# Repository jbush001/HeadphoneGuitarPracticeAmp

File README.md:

## Background

I was looking for a headphone guitar amp with the following features:

- Integrated guitar plug: Doesn't require an extra cable or have a box
  flopping around.
- Rechargeable battery
- Flexible set of basic effects with decent quality: distortion, reverb,
  amp simulation, etc.
- Built-in metronome

Although there are a number of commercially available headphone amps that
each support some of  these, surprisingly, none supported all of them, so
I decided to build my own. The heart of this is an ARM microcontroller,
which processes the audio signal and applies digital effects. The hardware
consists of a custom printed circuit board in a 3D printed enclosure.

## Setup (MacOS)

### Initial bits

Set up the environment (only required once)

    ./setup.sh

### CAD

This uses the build123d package for all CAD design. When starting a new terminal/session:

    source ./venv/bin/activate

You can regenerate the generated STL file by typing:

    python enclosure.py

The STL file can be viewed with a system viewer.

(Note, this may not work from the VSCode terminal, as it needs to separately set
the python environment).

### Schematic

Install the latest version of KiCAD from here <https://www.kicad.org/download/>.

Launch the editor, then, from the main project window, launch the
"Plugin and Content Manager." Search for "Fabrication Toolkit," and
click install, followed by "apply pending changes."

The fabrication toolkit is important not only because it fixes component
orientation differences between KiCad's symbols (which follow the IPC standard),
and JLCPCB's <https://jlcpcb.com/> library, which is based on the orientation
in the tape reel. If components are still misaligned (which can be seen from
the preview on JLCPCB's website), add the field FT Rotation Offset to the
symbol properties (it will rotate the field counter clockwise).

The fabrication outputs can be generated by clicking
Tools->External Plugins->Fabrication Toolkit from the PCB viewer. Output files
will be in the directory logic_board/production. The ones that are needed by
JLCPCB are:
- logic_board.zip. Upload using the 'Add Gerber' button
- bom.csv. After turning on the PCB Assembly switch and clicking next, can
  choose this file under the 'upload BOM' button.
- positions.csv. This is uploaded under the 'upload CPL' button.

Some through hole parts need to be hand soldered and are not included in the
assembly positions or BOM.

When changing part values or adding new parts, be sure to populate the
LCSC Part Number (note: case sensitive) attribute on the Symbol Properties
pane *from the schematic editor* (these will be copied to the PCB when
"Update PCB From Schematic" is pressed)

### Software

Software can be uploaded using the ST-Link v2 programmer (these are available in lots
of places).

<https://www.adafruit.com/product/2548?srsltid=AfmBOoq6BzHUY0KrrB4XPQAl0OvnK3d9qYIsi6UlSETSzX4CNc_bk4Xj>

This uses a standard SOICBite connector for debugging (e.g.
<https://www.pomonaelectronics.com/products/test-clips/ic-test-clips/soic-clip-8-pin>),
with the following pinout:

| Board Pad | Function    | ST-Link Pin |
|-----------|-------------|-------------|
|     1     | VCC (3.3v)  |     n/c     |
|     2     | SWDIO       |      2      |
|     3     | SWCLK       |      6      |
|     4     | GND         |      3      |
|     5     | UART TX     |      -      |
|     6     | UART RX     |      -      |
|     7     | nRST        |      1      |
|     8     | GPIO        |      -      |

Note: for the cheapo aluminum STLink clones, you don't want to connect VCC.

For UART, a serial to USB converter like
<https://www.deshide.com/product-details_SH-U09C2.html> can be used. It must be
set for 3.3v output. Connect the TX pin on the converter to the RX pin on the
board and vice versa. You'll need a Dupont Y jumper to share the ground
between the two connectors.

This uses the STM32H7 microcontroller.

Install ARM toolchain (MacOS)

    brew tap ArmMbed/homebrew-formulae
    brew install arm-none-eabi-gcc stlink

(Linux):

    sudo apt-get install gcc-arm-none-eabi binutils-arm-none-eabi

### Notebooks

    jupyter notebook notebooks/<notebook name>

(Select .venv as the kernel if asked)

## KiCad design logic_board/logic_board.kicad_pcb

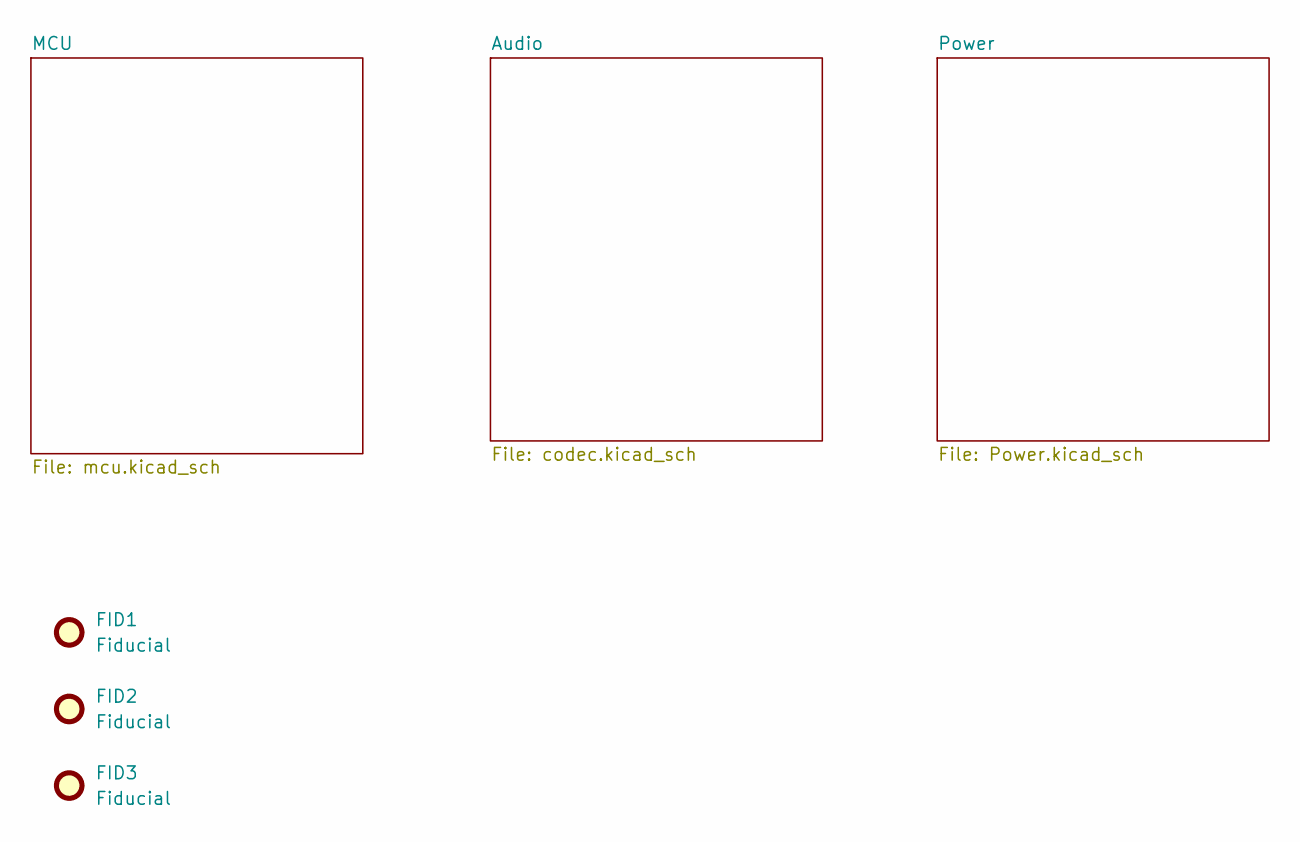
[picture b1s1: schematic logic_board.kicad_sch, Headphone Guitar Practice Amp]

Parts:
FID1, FID2, FID3: Fiducial; Fiducial_0.5mm_Mask1mm

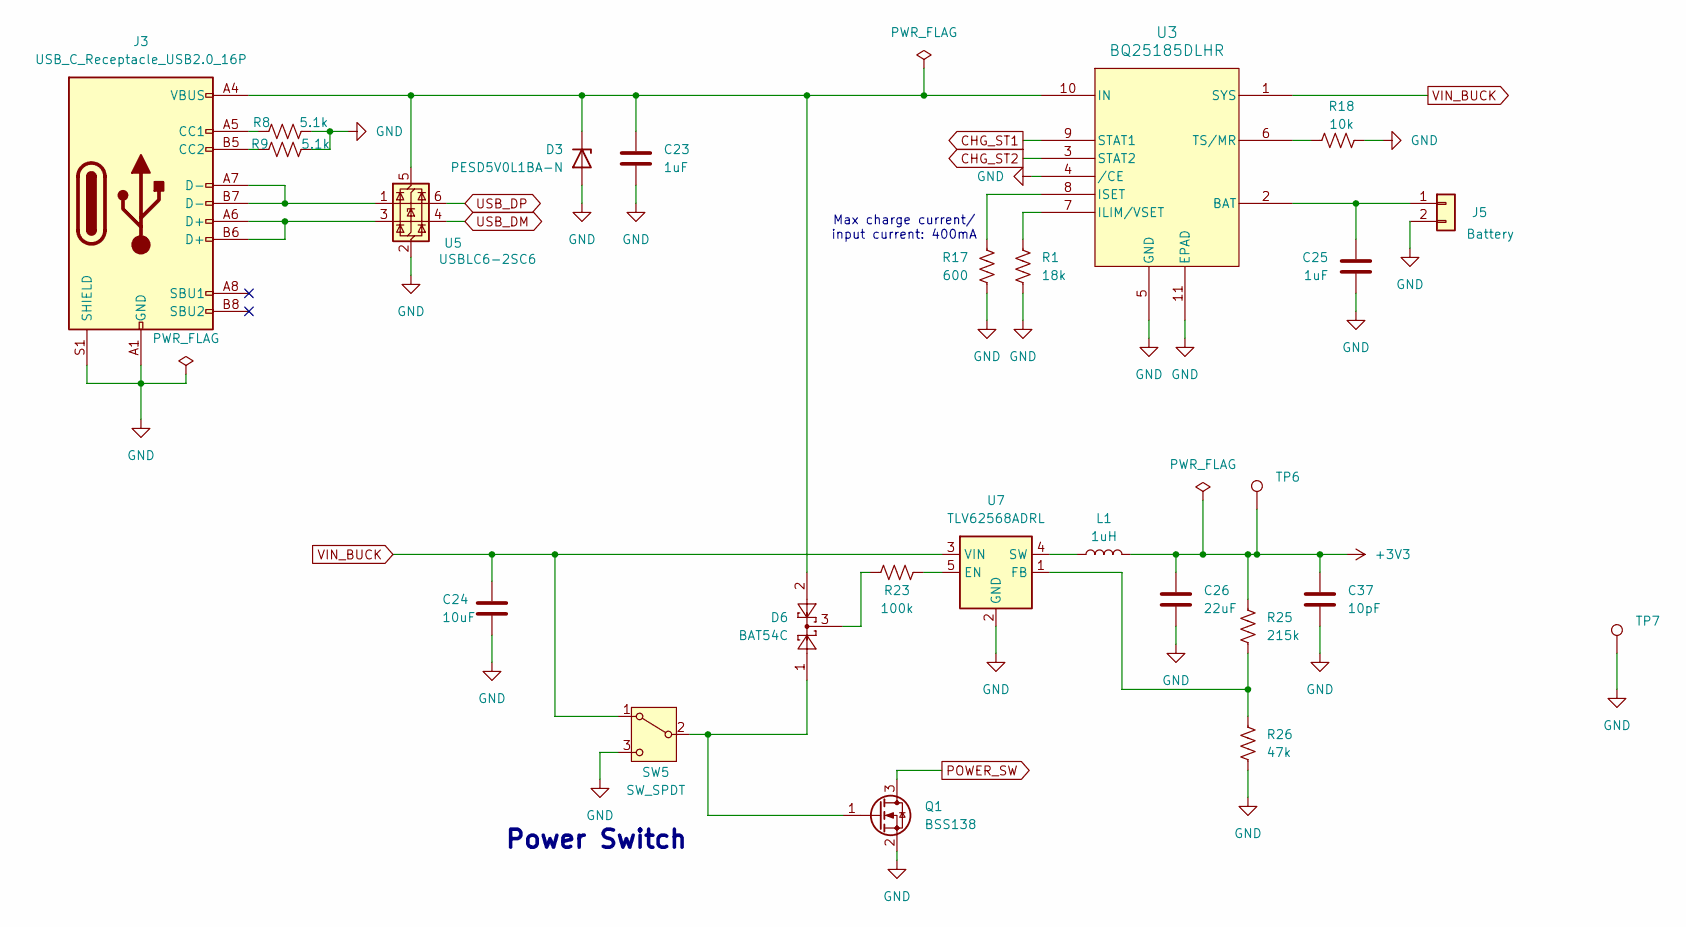
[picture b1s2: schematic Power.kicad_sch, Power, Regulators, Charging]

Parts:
C23, C25: 1uF; C_0603_1608Metric; LCSC Part Number C15849
C24: 10uF; C_0805_2012Metric; LCSC Part Number C15850
C26: 22uF; C_0805_2012Metric; LCSC Part Number C45783
C37: 10pF; C_0603_1608Metric; LCSC Part Number C1634
D3: PESD5V0L1BA-N; D_SOD-323; LCSC Part Number C920305
D6: BAT54C; SOT-23; LCSC Part Number C22466350
J3: USB_C_Receptacle_USB2.0_16P; TYPE-C-31-M-12; LCSC Part Number C165948
J5: Battery; SolderWire-0.1sqmm_1x02_P3.6mm_D0.4mm_OD1mm
L1: 1uH; L_APV_ANR4010; LCSC Part Number C135261
Q1: BSS138; SOT-23; LCSC Part Number C7420339
R1: 18k; R_0603_1608Metric
R8, R9: 5.1k; R_0603_1608Metric; LCSC Part Number C23186
R17: 600; R_0603_1608Metric
R18: 10k; R_0603_1608Metric; LCSC Part Number C25804
R23: 100k; R_0603_1608Metric; LCSC Part Number C25803
R25: 215k; R_0603_1608Metric
R26: 47k; R_0603_1608Metric
SW5: SW_SPDT; Alps Alpine SSSS211603; LCSC Part Number C125040
TP6, TP7: TestPoint; TestPoint_Pad_D1.0mm
U3: BQ25185DLHR; WSON10_DLH_TEX; LCSC Part Number C19725033
U5: USBLC6-2SC6; SOT-23-6; LCSC Part Number C7519
U7: TLV62568ADRL; SOT-563; LCSC Part Number C398372

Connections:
+3V3: C26.1, C37.1, L1.2, R25.1, TP6.1; also elsewhere on the board
CHG_ST1: U3.9 (STAT1); also elsewhere on the board
CHG_ST2: U3.3 (STAT2); also elsewhere on the board
GND: C23.2, C24.2, C25.2, C26.2, C37.2, D3.2 (A), J3.A1 (GND), J3.A12 (GND), J3.B1 (GND), J3.B12 (GND), J3.S1 (SHIELD), J5.2, Q1.2 (S), R1.2, R8.2, R9.2, R17.2, R18.2, R26.2, SW5.3 (C), TP7.1, U3.4 (/CE), U3.5 (GND), U3.11 (EPAD), U5.2 (GND), U7.2 (GND); also elsewhere on the board
unnamed: C23.1, D3.1 (K), D6.2, J3.A4 (VBUS), J3.A9 (VBUS), J3.B4 (VBUS), J3.B9 (VBUS), U3.10 (IN), U5.5 (VBUS)
unnamed: D6.3, R23.1
unnamed: J3.A5 (CC1), R8.1
unnamed: J3.B5 (CC2), R9.1
unnamed: J3.A6 (D+), J3.B6 (D+), U5.3 (I/O2)
unnamed: J3.A7 (D-), J3.B7 (D-), U5.1 (I/O1)
unnamed: C25.1, J5.1, U3.2 (BAT)
unnamed: D6.1, Q1.1 (G), SW5.2 (B)
unnamed: R1.1, U3.7 (ILIM/VSET)
unnamed: R17.1, U3.8 (ISET)
unnamed: R18.1, U3.6 (TS/MR)
unnamed: R23.2, U7.5 (EN)
unnamed: R25.2, R26.1, U7.1 (FB)
unnamed: L1.1, U7.4 (SW)
POWER_SW: Q1.3 (D); also elsewhere on the board
USB_DM: U5.4 (I/O2); also elsewhere on the board
USB_DP: U5.6 (I/O1); also elsewhere on the board
VIN_BUCK: C24.1, SW5.1 (A), U3.1 (SYS), U7.3 (VIN)

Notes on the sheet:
Max charge current/ input current: 400mA
Power Switch

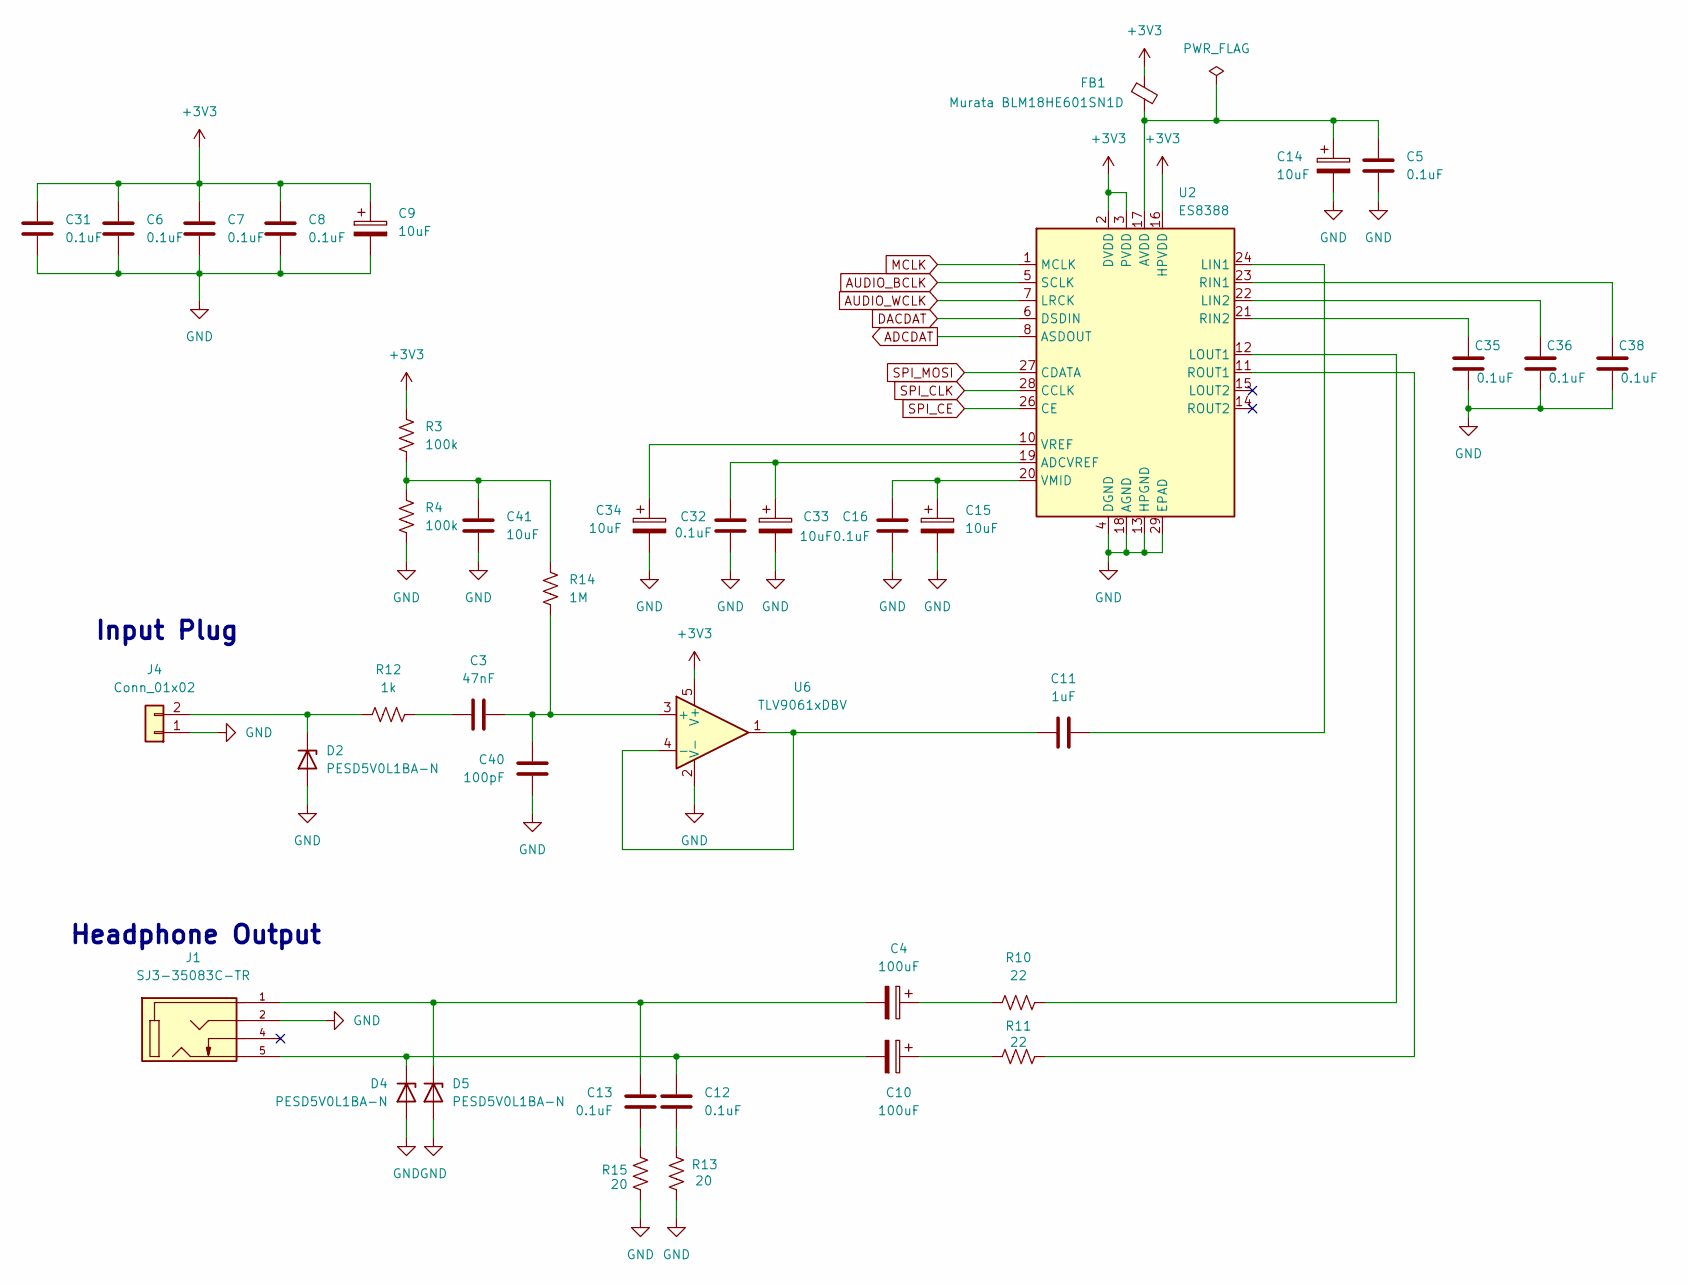
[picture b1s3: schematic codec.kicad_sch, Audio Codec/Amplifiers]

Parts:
C3: 47nF; C_0603_1608Metric; LCSC Part Number C1622
C4, C10: 100uF; C_1206_3216Metric; LCSC Part Number C15008
C5, C6, C7, C8, C12, C13, C16, C31, C32, C35, C36, C38: 0.1uF; C_0603_1608Metric; LCSC Part Number C14663
C9, C14, C15, C33, C34: 10uF; C_0805_2012Metric; LCSC Part Number C15850
C11: 1uF; C_0603_1608Metric; LCSC Part Number C15849
C40: 100pF; C_0603_1608Metric
C41: 10uF; C_0805_2012Metric
D2, D4, D5: PESD5V0L1BA-N; D_SOD-323; LCSC Part Number C920305
FB1: Murata BLM18HE601SN1D; L_0603_1608Metric; LCSC Part Number C88979
J1: SJ3-35083C-TR; SAMESKY_SJ3-35083C-TR; PARTREV 1.01; LCSC Part Number C9900193904
J4: Conn_01x02; SolderWire-0.1sqmm_1x02_P3.6mm_D0.4mm_OD1mm
R3, R4: 100k; R_0603_1608Metric
R10, R11: 22; R_0603_1608Metric; LCSC Part Number C23345
R12: 1k; R_0603_1608Metric; LCSC Part Number C21190
R13, R15: 20; R_0603_1608Metric; LCSC Part Number C22950
R14: 1M; R_0603_1608Metric; LCSC Part Number C22935
U2: ES8388; QFN-28-1EP_4x4mm_P0.45mm_EP2.6x2.6mm; LCSC Part Number C365736
U6: TLV9061xDBV; SOT-23-5; LCSC Part Number C398358

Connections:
+3V3: C6.1, C7.1, C8.1, C9.1, C31.1, FB1.1, R3.1, U2.2 (DVDD), U2.3 (PVDD), U2.16 (HPVDD), U6.5 (V+); also elsewhere on the board
ADCDAT: U2.8 (ASDOUT); also elsewhere on the board
AUDIO_BCLK: U2.5 (SCLK); also elsewhere on the board
AUDIO_WCLK: U2.7 (LRCK); also elsewhere on the board
DACDAT: U2.6 (DSDIN); also elsewhere on the board
GND: C5.2, C6.2, C7.2, C8.2, C9.2, C14.2, C15.2, C16.2, C31.2, C32.2, C33.2, C34.2, C35.1, C36.1, C38.1, C40.2, C41.2, D2.2 (A), D4.2 (A), D5.2 (A), J1.2, J4.1, R4.2, R13.2, R15.2, U2.4 (DGND), U2.13 (HPGND), U2.18 (AGND), U2.29 (EPAD), U6.2 (V-); also elsewhere on the board
MCLK: U2.1 (MCLK); also elsewhere on the board
unnamed: C3.1, R12.2
unnamed: C4.1, R10.1
unnamed: C10.1, R11.1
unnamed: C12.2, R13.1
unnamed: C13.2, R15.1
unnamed: C41.1, R3.2, R4.1, R14.1
unnamed: D2.1 (K), J4.2, R12.1
unnamed: C10.2, C12.1, D4.1 (K), J1.5
unnamed: C4.2, C13.1, D5.1 (K), J1.1
unnamed: C32.1, C33.1, U2.19 (ADCVREF)
unnamed: C5.1, C14.1, FB1.2, U2.17 (AVDD)
unnamed: C11.2, U2.24 (LIN1)
unnamed: C36.2, U2.22 (LIN2)
unnamed: R10.2, U2.12 (LOUT1)
unnamed: C38.2, U2.23 (RIN1)
unnamed: C35.2, U2.21 (RIN2)
unnamed: R11.2, U2.11 (ROUT1)
unnamed: C15.1, C16.1, U2.20 (VMID)
unnamed: C34.1, U2.10 (VREF)
unnamed: C3.2, C40.1, R14.2, U6.3 (+)
unnamed: C11.1, U6.1, U6.4 (-)
SPI_CE: U2.26 (CE); also elsewhere on the board
SPI_CLK: U2.28 (CCLK); also elsewhere on the board
SPI_MOSI: U2.27 (CDATA); also elsewhere on the board

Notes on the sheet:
Headphone Output
Input Plug

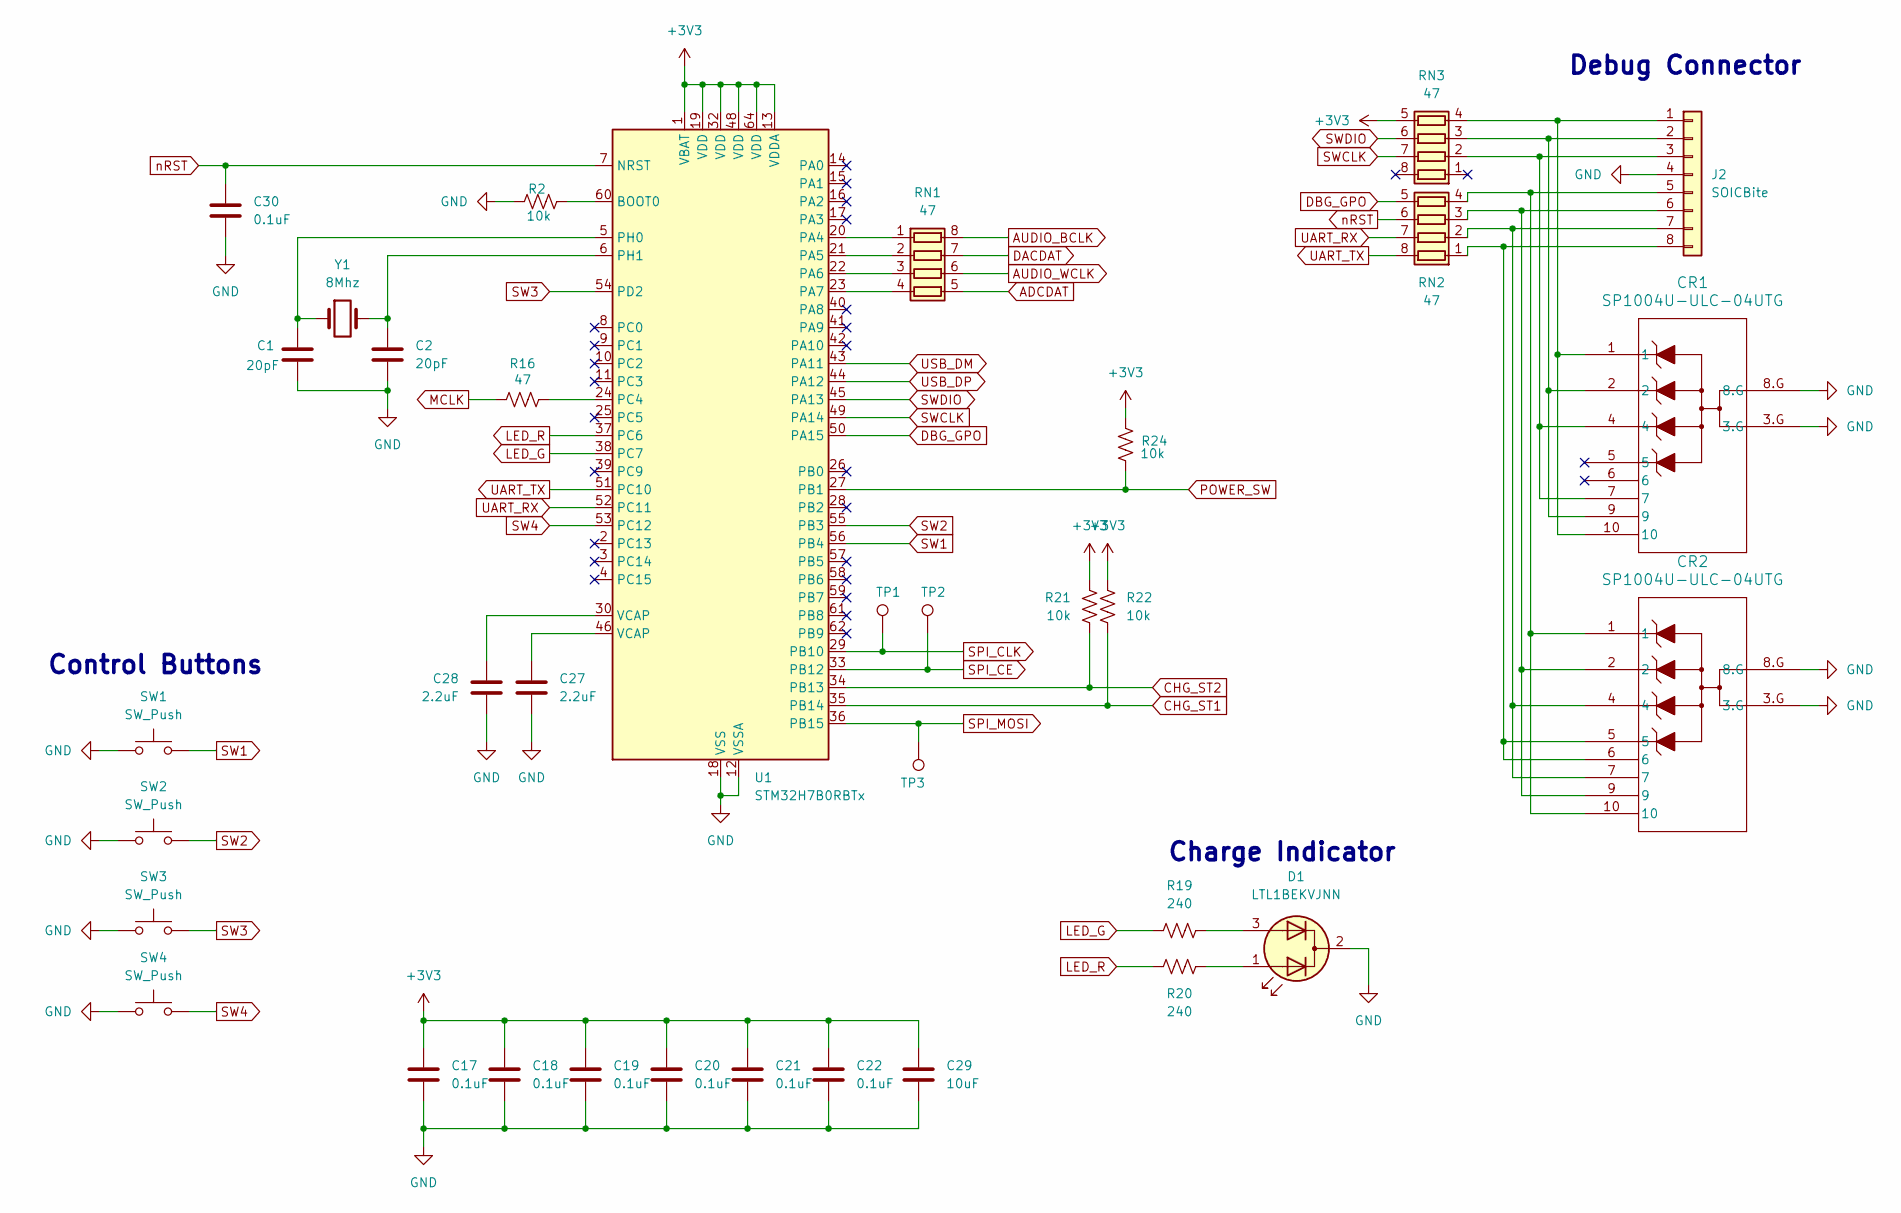
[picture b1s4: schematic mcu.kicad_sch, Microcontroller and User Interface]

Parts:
C1, C2: 20pF; C_0603_1608Metric; LCSC Part Number C1648
C17, C18, C19, C20, C21, C22, C30: 0.1uF; C_0603_1608Metric; LCSC Part Number C14663
C27, C28: 2.2uF; C_0603_1608Metric; LCSC Part Number C23630
C29: 10uF; C_0805_2012Metric; LCSC Part Number C15850
CR1, CR2: SP1004U-ULC-04UTG; 1004DFN_LTF; LCSC Part Number C1975518
D1: LTL1BEKVJNN; LED_D5.0mm-3
J2: SOICBite; SOIC_clipProgSmall
R2, R21, R22, R24: 10k; R_0603_1608Metric; LCSC Part Number C25804
R16: 47; R_0603_1608Metric
R19, R20: 240; R_0603_1608Metric; LCSC Part Number C23350
RN1, RN2, RN3: 47; R_Array_Concave_4x0603; LCSC Part Number C16081
SW1, SW2, SW3, SW4: SW_Push; SW_SPST_PTS645Sx43SMTR92; LCSC Part Number C83916
TP1, TP2, TP3: TestPoint; TestPoint_Pad_D1.0mm
U1: STM32H7B0RBTx; LQFP-64_10x10mm_P0.5mm; LCSC Part Number C730226
Y1: 8Mhz; Crystal_SMD_5032-2Pin_5.0x3.2mm; LCSC Part Number C115962

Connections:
+3V3: C17.1, C18.1, C19.1, C20.1, C21.1, C22.1, C29.1, R21.1, R22.1, R24.2, RN3.5 (R4.2), U1.1 (VBAT), U1.13 (VDDA), U1.19 (VDD), U1.32 (VDD), U1.48 (VDD), U1.64 (VDD); also elsewhere on the board
ADCDAT: RN1.5 (R4.2); also elsewhere on the board
AUDIO_BCLK: RN1.8 (R1.2); also elsewhere on the board
AUDIO_WCLK: RN1.6 (R3.2); also elsewhere on the board
CHG_ST1: R22.2, U1.35 (PB14); also elsewhere on the board
CHG_ST2: R21.2, U1.34 (PB13); also elsewhere on the board
DACDAT: RN1.7 (R2.2); also elsewhere on the board
DBG_GPO: RN2.5 (R4.2), U1.50 (PA15)
GND: C1.2, C2.2, C17.2, C18.2, C19.2, C20.2, C21.2, C22.2, C27.2, C28.2, C29.2, C30.2, CR1.3.G, CR1.8.G, CR2.3.G, CR2.8.G, D1.2 (K), J2.4, R2.1, SW1.1, SW2.1, SW3.1, SW4.1, U1.12 (VSSA), U1.18 (VSS), U1.31 (VSS), U1.47 (VSS), U1.63 (VSS); also elsewhere on the board
LED_G: R19.1, U1.38 (PC7)
LED_R: R20.1, U1.37 (PC6)
MCLK: R16.1; also elsewhere on the board
unnamed: C27.1, U1.46 (VCAP)
unnamed: C28.1, U1.30 (VCAP)
unnamed: D1.1 (A1), R20.2
unnamed: D1.3 (A2), R19.2
unnamed: CR1.1, CR1.10, J2.1, RN3.4 (R4.1)
unnamed: CR1.2, CR1.9, J2.2, RN3.3 (R3.1)
unnamed: CR1.4, CR1.7, J2.3, RN3.2 (R2.1)
unnamed: CR2.1, CR2.10, J2.5, RN2.4 (R4.1)
unnamed: CR2.2, CR2.9, J2.6, RN2.3 (R3.1)
unnamed: CR2.4, CR2.7, J2.7, RN2.2 (R2.1)
unnamed: CR2.5, CR2.6, J2.8, RN2.1 (R1.1)
unnamed: RN1.1 (R1.1), U1.20 (PA4)
unnamed: RN1.2 (R2.1), U1.21 (PA5)
unnamed: RN1.3 (R3.1), U1.22 (PA6)
unnamed: RN1.4 (R4.1), U1.23 (PA7)
unnamed: R2.2, U1.60 (BOOT0)
unnamed: R16.2, U1.24 (PC4)
unnamed: C1.1, U1.5 (PH0), Y1.1
unnamed: C2.1, U1.6 (PH1), Y1.2
POWER_SW: R24.1, U1.27 (PB1); also elsewhere on the board
SPI_CE: TP2.1, U1.33 (PB12); also elsewhere on the board
SPI_CLK: TP1.1, U1.29 (PB10); also elsewhere on the board
SPI_MOSI: TP3.1, U1.36 (PB15); also elsewhere on the board
SW1: SW1.2, U1.56 (PB4)
SW2: SW2.2, U1.55 (PB3)
SW3: SW3.2, U1.54 (PD2)
SW4: SW4.2, U1.53 (PC12)
SWCLK: RN3.7 (R2.2), U1.49 (PA14)
SWDIO: RN3.6 (R3.2), U1.45 (PA13)
UART_RX: RN2.7 (R2.2), U1.52 (PC11)
UART_TX: RN2.8 (R1.2), U1.51 (PC10)
USB_DM: U1.43 (PA11); also elsewhere on the board
USB_DP: U1.44 (PA12); also elsewhere on the board
nRST: C30.1, RN2.6 (R3.2), U1.7 (NRST)

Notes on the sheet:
Control Buttons
Debug Connector
Charge Indicator

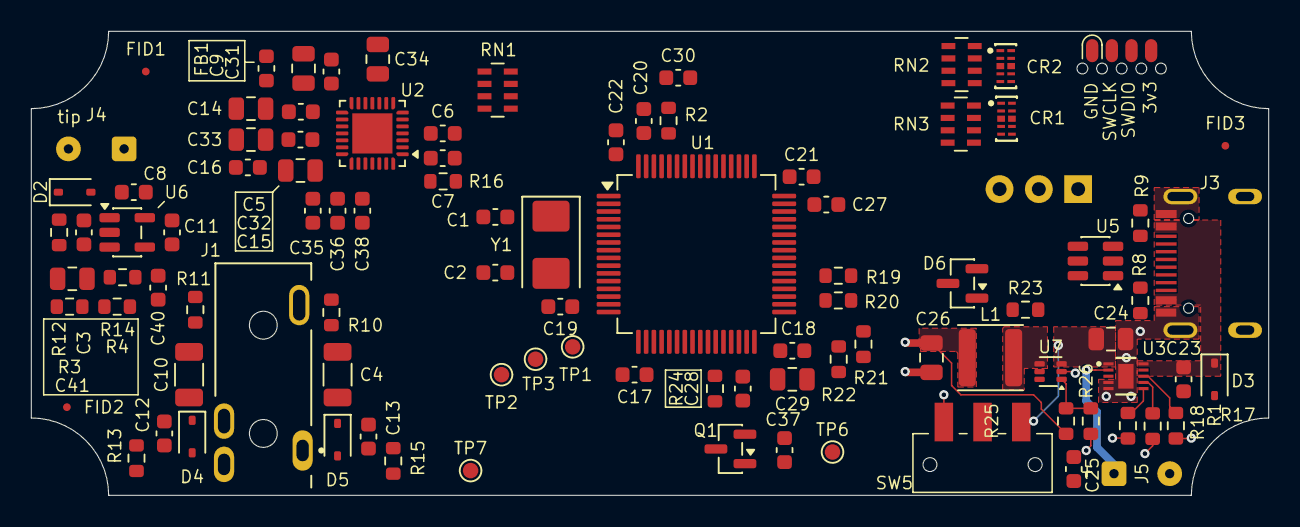
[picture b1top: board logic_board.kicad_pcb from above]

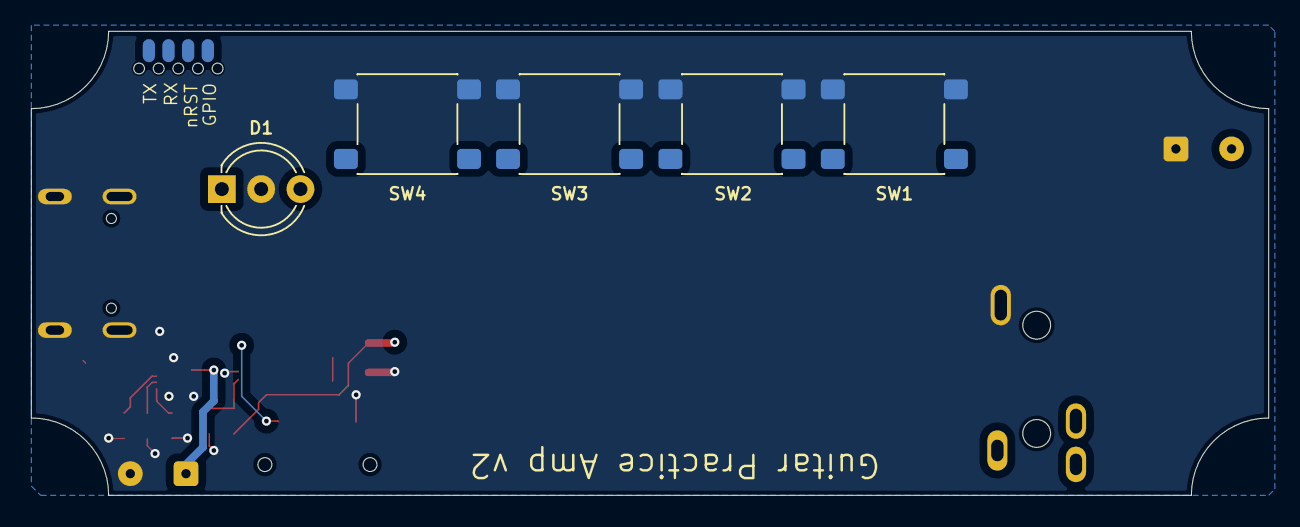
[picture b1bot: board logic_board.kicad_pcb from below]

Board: 4 copper layers, 80.0 x 30.0 mm, 102 parts (5 on the bottom side), 82 nets.

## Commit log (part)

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2020-01-26 Initial check-in
2020-01-27 Some physical modifications to the board.
    - Round the corners of the board so it will fit in an enclosure that is less blocky.
    - Move the headphone jack to the back of the housing instead of the side. It could
    have gotten in the way in some configurations in the old position.
    - Realign the push buttons. I had hand placed them, so the distances between them were
    not completely even before. This will make it a bit easier to design the enclosure.
    - Add a BOM list with DigiKey links that I used to find component footprints.
2020-01-27 Add an edge notch for the headphone jack in its new placement,
2020-01-28 Basic enclosure
2020-01-29 Re-layout board
    Slightly different dimensions and components placed on round-number
    offsets.
2020-01-30 Move in-pad vias off for small components, with a small trace.
    I realized for the 0402 components, there wasn't a lot of copper
    to solder onto, especially when both pads had vias in them.
2020-01-31 Add silk screen board name.
2020-02-01 Minor cleanup
    Move silk screened references so they don't get broken by vias.
    Move some components to give a little more breathing room.
    Fix some traces to be straighter.
2020-02-01 Update BOM
    Move power/charge LEDs back from edge so there's enough room. Use horizontal footprint.
2020-02-01 Pull BOOT0 pin down by default to boot from flash
    Also thickened some power traces to MPU.
2020-02-01 Clean up BOM
2020-02-01 Convert BOM to markdown
2020-02-02 Update enclosure
    The previous one wouldn't fit well in a strat with it's recessed jack.
    Also moved some footprints on the PCB to have more consistent spacing.
2020-02-02 Get rid of AP3419 from custom parts library
    I switched from it because it was EOL
2020-02-02 A few other enclosure improvements: - Use a chamfer instead of radius on the top and bottom edges. Whichever ones are parallel to the bed will always end up looking like chamfers anyway. - Make the p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
2020-02-02 A few other enclosure fixes
    - Needed to notch lip on top enclosure around holes
    - Due to making lip smaller, needed to increase height parameters
    for top and bottom to maintain total height.
    - Widen power switch opening
    Deleted Cura project, as I was having trouble with stale models.
2020-02-02 Update STL for top enclosure.
2020-02-02 Improve decal a little, use icons instead of text
    I just hand coded these in SVG. They need a little tweaking and cleanup.
2020-02-03 A few enclosure fixes based on 2nd test print
    - Position of buttons on decal was offset
    - Make the top of the buttons rounded.
    - The base of the buttons needs a smaller radius, otherwise they interfere.
    - Increase size of overlap lip.
    - Increase length of top bosses
2020-02-03 Clean up icons on decal
    Also make the lower bosses extend to the bottom of the shell. This shouldn't have any
    change in the final model.
2020-02-03 Try to make it look a bit nicer.
2020-02-03 A little more decal cleanup
    Make icons a bit larger, align. Use groups to make it easier to modify.
2020-02-03 Fix a few Digikey links
2020-02-03 Make counterbore holes deeper
    I had made the upper bosses a bit longer, but hadn't adjusted the
    counterbores. The result is that the screws wouldn't engage as
    deeply. Change so the counterbore depth is relative to the bottom
    of the boss instead of the case height.
    Also tweaked some dimensions to make sure the screw head has enough plastic
    to hold onto, but these may be below the abilities of the printer anyway.
2020-02-04 Update STL files
2020-02-04 Change label outside radius to match enclosure
2020-02-04 Update STL
2020-02-05 Update STL models
2020-02-05 Button had invalid geometry.
    Increase outer thickness.
2020-02-05 Make the label slightly smaller than the cutout in the top enclosure.
2020-02-05 Fix label border
2020-02-05 Add layout PDF
2020-02-06 Minimal firmware build
2020-02-08 Switch to a microcontroller with more SRAM
    This is necessary to enable some effects like reverb and echo.
    This part has a similar pinout, but not exactly the same, which required some layout
    changes.
    I also took this opportuntity to move the serial pins to a separate header with its
    own ground, which makes connecting a serial debugger and SWD interface at the same
    time easier.
2020-02-08 Fix a few incorrect MCU pin connections from last change.
2020-02-08 Fix button icon positioning after previous cutout fix.
2020-02-09 PCB layout cleanup
2020-02-09 Add blinkenlights for debugging
2020-02-09 Remove external pullups.
    The chip already has internal ones.
2020-02-09 Remove USB series termination resistors
    Page 179 of the datasheet states: "No external termination series
    resistors are required on USB_PD P(D+) and USB_DM (D-); the matching
    impedance is already included in the embedded driver." (There's a typo,
    presumably they meant USB_DP).
2020-02-09 Connect VBAT to VDD
    From AN5096, "If no external battery is used in the application, it is recommended
    to connect VBAT externally to VDD."
2020-02-09 Move resonator closer to MCU.
2020-02-09 Move I2C2_SDA from PA8 to PA10
    There is conflicting information in the datahsheet. Table 13 says this
    should be PA10, but Table 12 says PA8. I'm using the former, as it
    has actual mappings. This would be fairly easy to rework with a blue
    wire if I guessed wrong: jumpering the pins together and making PA10
    be an input.
2020-02-09 Route USB data lines away from MCU resonator
2020-02-09 Move vias off pads
    Having a via on a pad can complicate soldering because the vias wick away
    solder.
2020-02-09 A little more board cleanup
    Move some vias off pads that I missed in the last change.
    Clean up silk screened references.
2020-02-09 Basic blinky test app.
2020-02-09 Nitpicky routing cleanup
2020-02-10 Enable clocks to GPIO block in blinking program.
    I won't be able to test this until I get the boards back and assemble them, so this
    is speculative based on datasheets for now.
2020-02-10 Leave a small via connected to pin PA8.
    There is a contradiction in the datasheet between two tables. I've taken an educated guess,
    but if that is wrong, this will make it easier to rework.
2020-02-10 Update BOM
2020-02-14 Use longer screws
    The M2x6 screws are too short with the PCB in place. This requires upgrading to M2.3 screws.
    Increased bore sizes. I had to make the top bosses tapered to accomodate the larger counterbore.
    I tapered the bottom ones just to match.
    Also increased the RELIEF to 0.8, as the parts do warp a bit and things stick during assembly.
2020-02-16 Nitpicky layout cleanup and alignment
2020-02-18 Update STL files to go along with last change.
2020-02-18 Make C25 a no-stuff, and other layout improvements
    C25 was a leftover from when there was a switching regulator.
2020-02-19 Clean up linker file and initialization.
2020-02-27 Add LICENSE
2020-03-05 Fix I2C2_SDA, which was mislabeled in the STM32G473 datasheet.
    It now connects to pin30. In the G474 datasheet, both places
    that reference this pin agree.
2020-03-10 The custom footprint for the tactile had the pins misnumbered
    They were rotated 90 degrees. There are actually four pins, with
    two on each side connected internally. There doesn't seem to be
    an easy way to indicate that in kicad, so only two are connected
    to the schematic symbol.
2020-03-16 Update all 0402 SMD packages to 0603
    Mainly to make soldering easier. 0402 was unnecessarily small.
2020-03-16 Update BOM based on new component sizes
2020-10-10 Add a small extension to the button to rest on the dome
    The flat bottom was hitting components on the board, so it couldn't actually
    depress the switch.
2021-07-07 Add schematic PDF and update some tool stuff.
2025-12-25 Add headphone jack
    Change PCB to proper size.
2025-12-25 Component selection
    Imported specific parts into KiCAD project library (including JLCPCB part numbers).
2025-12-25 Add more parts to schematic
2025-12-26 Ready for routing. - Lay out all components in proper positions - Add all support passives (bypass caps, etc) - Add board corner cutouts for enclosure bosses.
2025-12-26 Layout power supply section
    I swapped the regulator and debug connector to group the power supply components together.
2025-12-27 All signals now routed.
    A bit rough, needs some cleanup.
2025-12-27 Fix some incorrect footprints/symbols
2025-12-28 Power switch connects to en pin on LDO rather than switching power directly.
2025-12-28 More layout tweaks
2025-12-28 Added ferrite on codec analog power supply.
2025-12-29 Change how charge management is handled
    The LDO (and microcontroller) are now enabled even if the power switch is off when the device is charging.
    Added a bi-color LED to indicate charging status (driven by microcontroller)
    Charge status now routed to the microcontroller, as well as power switch status.
    (Note this would also allow data transfer to the microcontroller when plugged in when the power switch is off, which is probably desirable).
2025-12-29 Replace crystal with a more common variant, 8Mhz
2025-12-29 Modified pads on headset jack to fix DRC warnings
    I had imported Samesky's default footprint, but pins 4 and 5 had copper that was very close and in danger of bridging. I reduced the Y dimension of the pad so there is now 0.4mm betwen pads.
2025-12-30 Clean up some footprints
2025-12-30 More component placement tweaking, mostly around audio section.
2025-12-30 Standardize part values and flesh out documentation.
2025-12-30 Fix some DRC violations
2025-12-30 Clean up custom library symbols/footprints
    Remove unneeded, make silk screen designators more consistent/obvious
    Properly set pin types for ERC
2025-12-30 Add fiducials
2025-12-31 Basic skeleton of enclosure code.
2025-12-31 Fix some PCB issues
    TVS diodes had wrong footprint
    U5 was rotated 180 degrees in CPL file.
2025-12-31 Add test points, schematic annotations
2026-01-01 Set max charge current appropriately with resistor values.
2026-01-01 Change value of buck converter FB divider registers
    First reduce the values for less noise susceptibility and
    jitter, but also pick standard E24 values.
2026-01-01 Update component placement, fix all silk screen reference designators
2026-01-03 Lay out power supply section.
